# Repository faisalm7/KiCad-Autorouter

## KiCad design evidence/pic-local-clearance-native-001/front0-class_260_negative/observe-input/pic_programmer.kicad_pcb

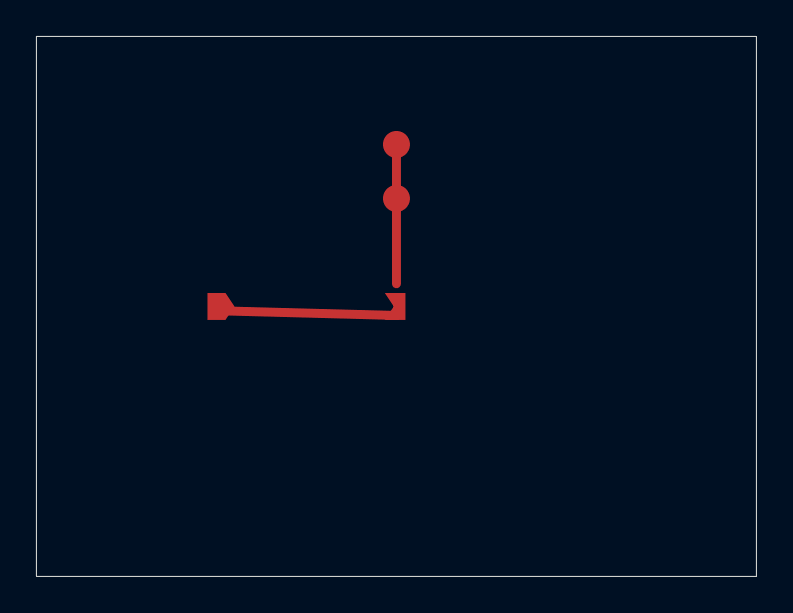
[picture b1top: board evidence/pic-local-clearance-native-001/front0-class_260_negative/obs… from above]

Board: 2 copper layers, 40.0 x 30.0 mm, 4 parts (0 on the bottom side), 2 nets.

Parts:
CONCAVE: Owned_CONCAVE
CONVEX: Owned_CONVEX
FOREIGN_A: Owned_FOREIGN_A
FOREIGN_B: Owned_FOREIGN_B

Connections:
FOREIGN: FOREIGN_A.1, FOREIGN_B.1
VCC: CONCAVE.1 (2_2), CONVEX.1 (1_1)

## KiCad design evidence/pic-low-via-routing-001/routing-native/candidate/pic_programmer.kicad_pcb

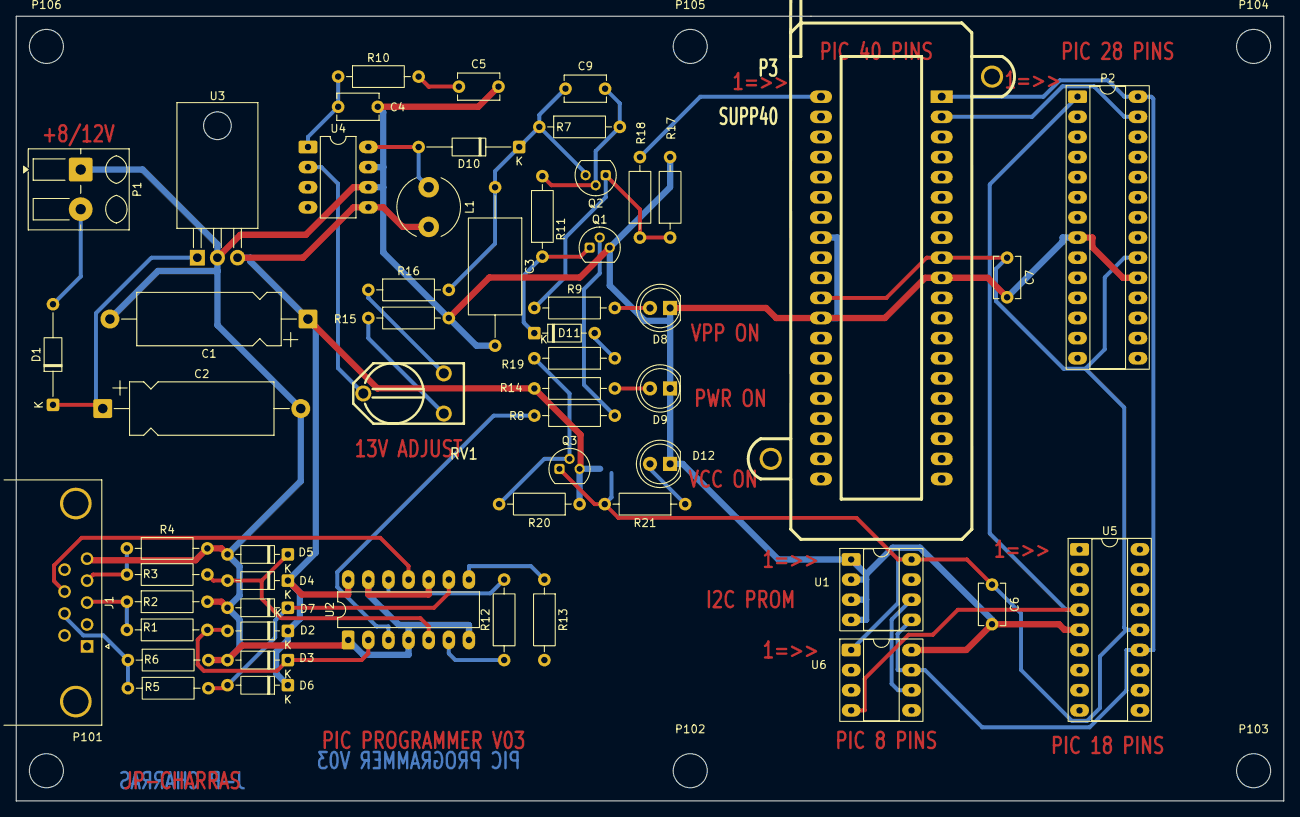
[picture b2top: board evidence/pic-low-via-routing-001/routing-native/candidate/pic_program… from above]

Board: 2 copper layers, 160.0 x 99.1 mm, 63 parts (1 on the bottom side), 34 nets.

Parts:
C1: 100µF; CP_Axial_L18.0mm_D6.5mm_P25.00mm_Horizontal
C2: 220uF; CP_Axial_L18.0mm_D6.5mm_P25.00mm_Horizontal
C3: 22uF/25V; C_Axial_L12.0mm_D6.5mm_P20.00mm_Horizontal
C4: 0; C_Disc_D5.1mm_W3.2mm_P5.00mm
C5: 10nF; C_Disc_D5.1mm_W3.2mm_P5.00mm
C6, C7: 100nF; C_Disc_D5.1mm_W3.2mm_P5.00mm
C9: 220nF; C_Disc_D5.1mm_W3.2mm_P5.00mm
D1: 1N4004; D_DO-35_SOD27_P12.70mm_Horizontal
D2, D3, D4, D5, D6, D7, D11: BAT43; D_DO-35_SOD27_P7.62mm_Horizontal
D8: RED-LED; LED_D5.0mm
D9: GREEN-LED; LED_D5.0mm
D10: SCHOTTKY; D_DO-35_SOD27_P12.70mm_Horizontal
D12: YELLOW-LED; LED_D5.0mm
J1: DB9-FEMAL; DSUB-9_Socket_Horizontal_P2.77x2.84mm_EdgePinOffset7.70mm_H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
JP1: JUMPER; SolderJumper-2_P1.3mm_Open_TrianglePad1.0x1.5mm
L1: 22uH; L_Radial_D7.8mm_P5.00mm_Fastron_07HCP
P1: CONN_2; Altech_AK300_1x02_P5.00mm_45-Degree
P2: SUPP28; DIP-28_W7.62mm_Socket_LongPads
P3: SUPP40; 40tex-Ell600
P101, P102, P103, P104, P105, P106: CONN_1; MountingHole_4.3mm_M4
Q1: BC237; TO-92
Q2, Q3: BC307; TO-92
R1, R2, R3, R4, R5, R6, R7: 10K; R_Axial_DIN0207_L6.3mm_D2.5mm_P10.16mm_Horizontal
R8: 1K; R_Axial_DIN0207_L6.3mm_D2.5mm_P10.16mm_Horizontal
R9, R19, R20: 2.2K; R_Axial_DIN0207_L6.3mm_D2.5mm_P10.16mm_Horizontal
R10: 5,1K; R_Axial_DIN0207_L6.3mm_D2.5mm_P10.16mm_Horizontal
R11, R17: 22K; R_Axial_DIN0207_L6.3mm_D2.5mm_P10.16mm_Horizontal
R12, R13, R14, R21: 470; R_Axial_DIN0207_L6.3mm_D2.5mm_P10.16mm_Horizontal
R15: 6.2K; R_Axial_DIN0207_L6.3mm_D2.5mm_P10.16mm_Horizontal
R16: 62K; R_Axial_DIN0207_L6.3mm_D2.5mm_P10.16mm_Horizontal
R18: 220; R_Axial_DIN0207_L6.3mm_D2.5mm_P10.16mm_Horizontal
RV1: 1K; RV2X4
U1: 24Cxx; DIP-8_W7.62mm_Socket_LongPads
U2: 74HC125; DIP-14_W7.62mm_LongPads
U3: 7805; TO-220-3_Horizontal_TabDown
U4: LT1373; DIP-8_W7.62mm_LongPads
U5: PIC_18_PINS; DIP-18_W7.62mm_Socket_LongPads
U6: PIC_8_PINS; DIP-8_W7.62mm_Socket_LongPads

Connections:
/CLOCK-RB6: P2.27, P3.39, R13.2, U1.6 (SCL), U5.12 (ICSPC/RB6), U6.6 (GP1)
/DATA-RB7: P2.28, P3.40, R12.2, U1.5 (SDA), U2.12, U5.13 (ICSPD/RB7), U6.7 (GP0)
/PC-CLOCK-OUT: J1.7, R5.1, R6.1
/PC-DATA-IN: J1.8, U2.11
/PC-DATA-OUT: J1.4, R3.1, R4.1
/VPP_ON: J1.3, R1.1, R2.1
/VPP/MCLR: P2.1, P3.1, R18.2, U5.4 (MCLR), U6.4 (GP3/MCLR)
/pic_sockets/VCC_PIC: C6.1, C7.1, JP1.2, P2.20, P3.11, P3.32, Q3.1 (C), R21.2, U1.8 (VCC), U5.14 (VDD), U6.1 (VDD)
GND: C1.2, C2.2, C3.2, C4.2, C5.2, C6.2, C7.2, D3.2 (A), D5.2 (A), D7.2 (A), D8.1 (K), D9.1 (K), D12.1 (K), J1.5, P1.1, P2.8, P2.19, P3.8, P3.12, P3.31, Q1.3 (E), R2.2, R4.2, R6.2, R15.2, R17.2, U1.1 (A0), U1.2 (A1), U1.3 (A2), U1.4 (GND), U2.1, U2.4, U2.7 (GND), U2.10, U2.13, U3.2 (GND), U4.6 (GND_S), U4.7 (GND), U5.5 (VSS), U6.8 (VSS)
unnamed: C5.1, R10.2
unnamed: D1.2 (A), P1.2 (PM)
unnamed: C2.1, D1.1 (K), U3.1 (VI)
unnamed: D2.2 (A), D3.1 (K), R1.2, U2.2
unnamed: D4.2 (A), D5.1 (K), R3.2, U2.5
unnamed: D6.2 (A), D7.1 (K), R5.2, U2.9
unnamed: D8.2 (A), R9.2
unnamed: D9.2 (A), R14.2
unnamed: D10.2 (A), L1.1, U4.8 (Vsw)
unnamed: D11.2 (A), R19.1
unnamed: D11.1 (K), Q1.1 (C), R11.1
unnamed: D12.2 (A), R21.1
unnamed: Q1.2 (B), R8.2
unnamed: C9.2, Q2.2 (B), R7.2, R11.2
unnamed: Q2.1 (C), R9.1, R17.1, R18.1
unnamed: Q3.2 (B), R19.2, R20.2
unnamed: R8.1, U2.3
unnamed: R12.1, U2.6
unnamed: R13.1, U2.8
unnamed: R15.1, RV1.1
unnamed: R16.1, RV1.3
unnamed: RV1.2, U4.2 (FB+)
unnamed: C4.1, R10.1, U4.1 (Vc)
VCC: C1.1, D2.1 (K), D4.1 (K), D6.1 (K), JP1.1, L1.2, Q3.3 (E), R14.1, R20.1, U2.14 (VCC), U3.3 (VO), U4.5 (Vin)
VPP: C3.1, C9.1, D10.1 (K), Q2.3 (E), R7.1, R16.2
